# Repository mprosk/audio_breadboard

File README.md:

# audio_breadboard
PCB backplate for breadboarding audio applications

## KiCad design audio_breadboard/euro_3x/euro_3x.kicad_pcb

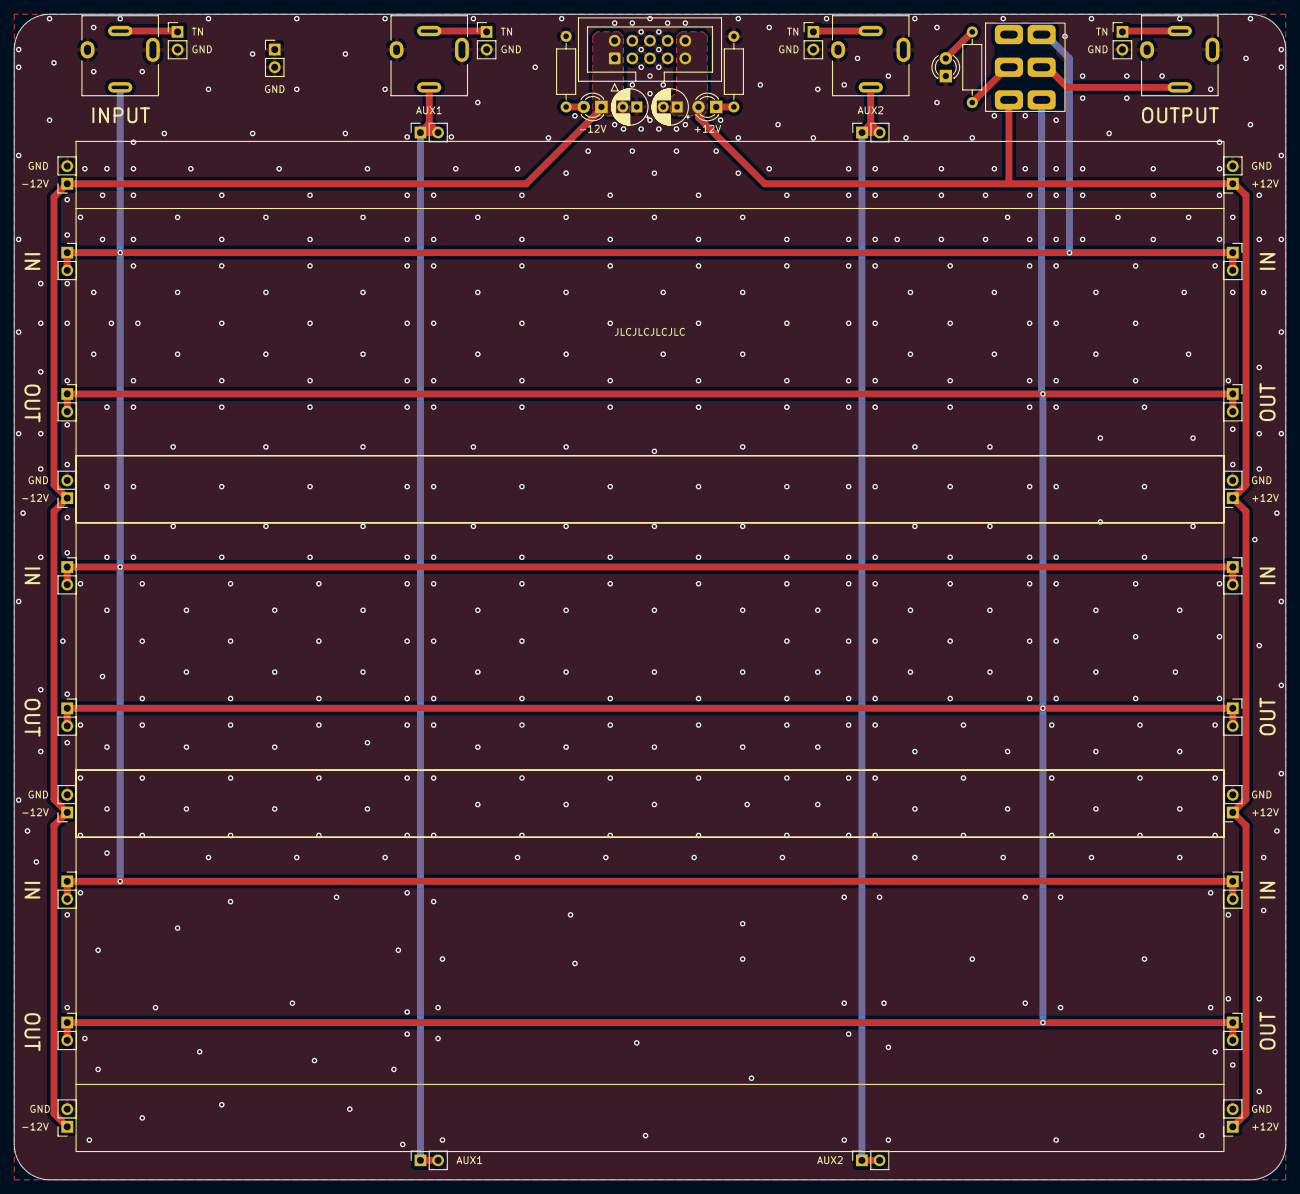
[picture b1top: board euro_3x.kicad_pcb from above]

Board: 2 copper layers, 182.9 x 167.6 mm, 46 parts (0 on the bottom side), 16 nets.

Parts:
B1, B2, B3: Breadboard
C1, C2: 100uF; CP_Radial_D5.0mm_P2.00mm
D1: +12V; LED_D3.0mm
D2: -12V; LED_D3.0mm
D3: ENABLE; LED_D3.0mm
J1: EURO POWER; IDC-Header_2x05_P2.54mm_Vertical
J2: INPUT; Jack_3.5mm_QingPu_WQP-PJ301BM
J3: OUTPUT; Jack_3.5mm_QingPu_WQP-PJ301BM
J4: AUX1; Jack_3.5mm_QingPu_WQP-PJ301BM
J5: AUX2; Jack_3.5mm_QingPu_WQP-PJ301BM
J6, J7, J19, J31: +12V; PinSocket_1x02_P2.54mm_Vertical
J8, J9, J20, J32: -12V; PinSocket_1x02_P2.54mm_Vertical
J10, J11, J16, J21, J27, J28: IN; PinSocket_1x02_P2.54mm_Vertical
J12, J13, J17, J22, J29, J30: OUT; PinSocket_1x02_P2.54mm_Vertical
J14, J23: AUX1; PinSocket_1x02_P2.54mm_Vertical
J15, J24: AUX2; PinSocket_1x02_P2.54mm_Vertical
J18: GND; PinHeader_1x02_P2.54mm_Vertical
JP1, JP2, JP3, JP4: TN_GND; PinHeader_1x02_P2.54mm_Vertical
R1, R2, R3: 1k2; R_Axial_DIN0207_L6.3mm_D2.5mm_P10.16mm_Horizontal
SW1: SW_DPDT_x2; Switch_DPDT

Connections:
+12V: C1.1, D1.2 (A), J1.9, J1.10, J6.1, J7.1, J19.1, J31.1, SW1.3 (C)
-12V: C2.2, D2.1 (K), J1.1, J1.2, J8.1, J9.1, J20.1, J32.1
/AUX1: J4.T, J14.1, J14.2, J23.1, J23.2
/AUX2: J5.T, J15.1, J15.2, J24.1, J24.2
/EN: R3.1, SW1.2 (B)
/INPUT: J2.T, J10.1, J10.2, J11.1, J11.2, J16.1, J16.2, J21.1, J21.2, J27.1, J27.2, J28.1, J28.2, SW1.4 (A)
/OUTPUT: J3.T, SW1.5 (B)
/TN_AUX1: J4.TN, JP3.1 (A)
/TN_AUX2: J5.TN, JP4.1 (A)
/TN_IN: J2.TN, JP1.1 (A)
/TN_OUT: J3.TN, JP2.1 (A)
/TO_OUT: J12.1, J12.2, J13.1, J13.2, J17.1, J17.2, J22.1, J22.2, J29.1, J29.2, J30.1, J30.2, SW1.6 (C)
GND: C1.2, C2.1, D3.1 (K), J1.3, J1.4, J1.5, J1.6, J1.7, J1.8, J2.S, J3.S, J4.S, J5.S, J6.2, J7.2, J8.2, J9.2, J18.1, J18.2, J19.2, J20.2, J31.2, J32.2, JP1.2 (B), JP2.2 (B), JP3.2 (B), JP4.2 (B), R1.2, R2.1
unnamed: D1.1 (K), R1.1
unnamed: D2.2 (A), R2.2
unnamed: D3.2 (A), R3.2

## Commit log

2023-12-25 add kosmo-lib and up-rev
2023-12-25 Complete schematic and layout
2023-12-25 export gerbers for euro_1x
2023-12-25 Complete Euro 2x
2023-12-25 start euro 3x layout
2023-12-29 fix breadboard footprint
2024-01-14 Update breadboard in kosmo-lib
2024-01-14 Fix euro1x with latest breadboard footprint
2024-01-15 Finalize board layouts
2024-01-15 Add pcb_v0.1 gerber files
